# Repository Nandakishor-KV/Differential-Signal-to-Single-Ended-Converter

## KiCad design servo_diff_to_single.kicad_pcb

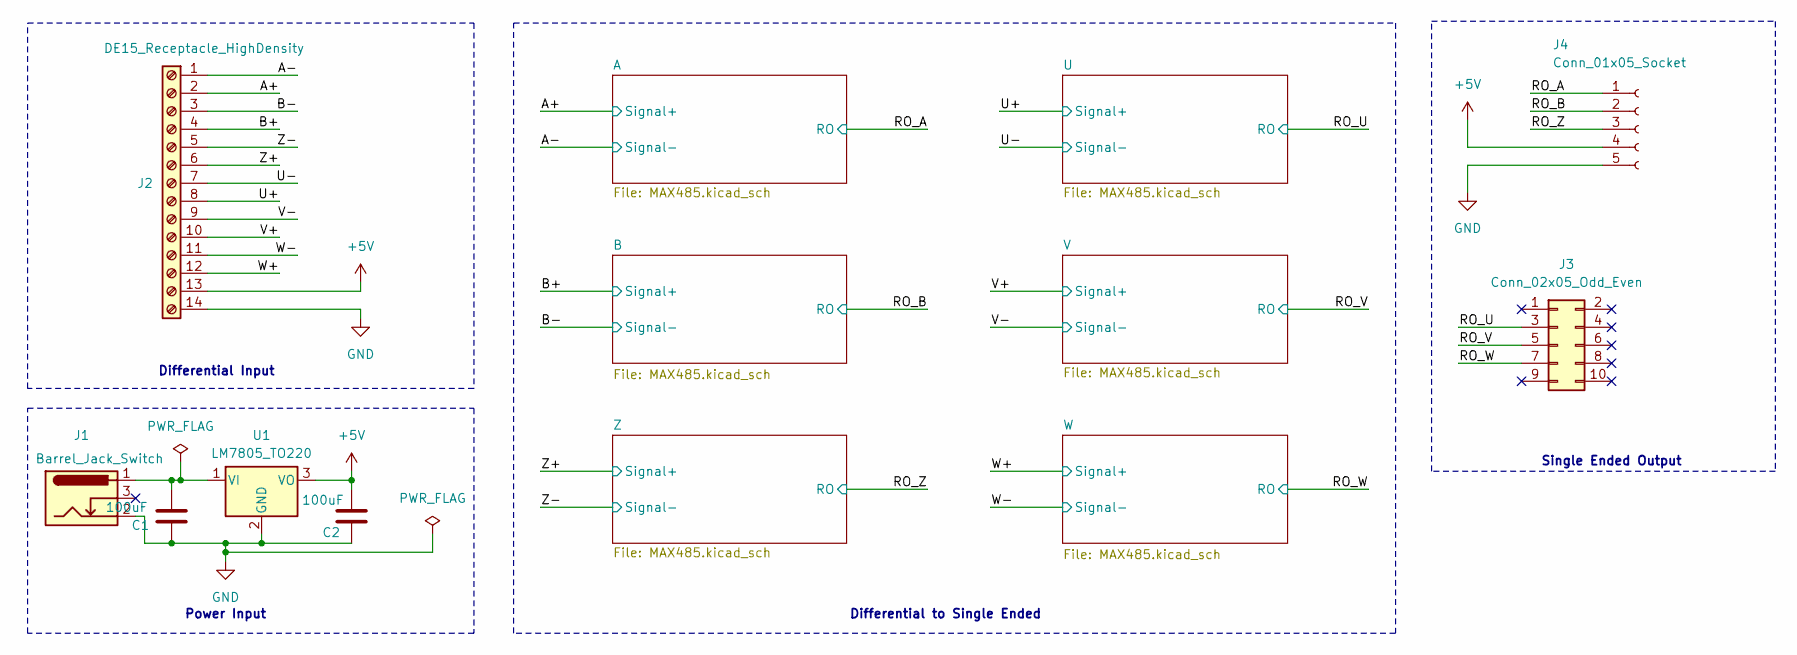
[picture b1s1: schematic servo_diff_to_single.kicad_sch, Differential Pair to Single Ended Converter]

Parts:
C1, C2: 100uF; CP_Radial_D6.3mm_P2.50mm
J1: Barrel_Jack_Switch; BarrelJack_Horizontal
J2: DE15_Receptacle_HighDensity; TerminalBlock_Phoenix_MKDS-3-14-5.08_1x14_P5.08mm_Horizontal
J3: Conn_02x05_Odd_Even; IDC-Header_2x05_P2.54mm_Vertical
J4: Conn_01x05_Socket; PinSocket_1x05_P2.54mm_Vertical
U1: LM7805_TO220; TO-220-3_Vertical_HS48_PL48_Heatsink_Without_mounting

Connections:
+5V: C2.1, J2.13, J4.4, U1.3 (VO); also elsewhere on the board
/A+: J2.2; also elsewhere on the board
/A-: J2.1; also elsewhere on the board
/B+: J2.4; also elsewhere on the board
/B-: J2.3; also elsewhere on the board
/RO_A: J4.1; also elsewhere on the board
/RO_B: J4.2; also elsewhere on the board
/RO_U: J3.3; also elsewhere on the board
/RO_V: J3.5; also elsewhere on the board
/RO_W: J3.7; also elsewhere on the board
/RO_Z: J4.3; also elsewhere on the board
/U+: J2.8; also elsewhere on the board
/U-: J2.7; also elsewhere on the board
/V+: J2.10; also elsewhere on the board
/V-: J2.9; also elsewhere on the board
/W+: J2.12; also elsewhere on the board
/W-: J2.11; also elsewhere on the board
/Z+: J2.6; also elsewhere on the board
/Z-: J2.5; also elsewhere on the board
GND: C1.2, C2.2, J1.2, J2.14, J4.5, U1.2 (GND); also elsewhere on the board
unnamed: C1.1, J1.1, U1.1 (VI)

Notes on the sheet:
Differential to Single Ended
Power Input
Single Ended Output
Differential Input

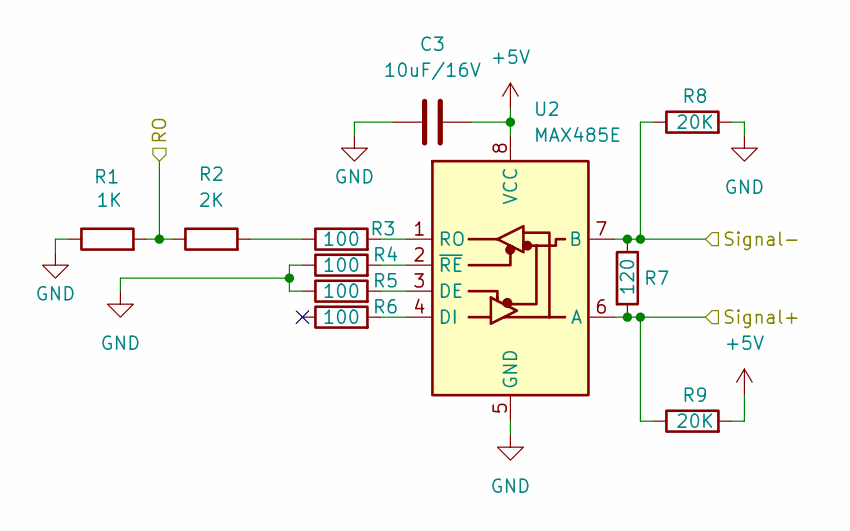
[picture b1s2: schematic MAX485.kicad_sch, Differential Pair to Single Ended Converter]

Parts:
C3: 10uF/16V; CP_Radial_D5.0mm_P2.50mm
R1: 1K; 0.25W_resistor
R2: 2K; 0.25W_resistor
R3, R4, R5, R6: 100; 0.25W_resistor
R7: 120; 0.25W_resistor
R8, R9: 20K; 0.25W_resistor
U2: MAX485E; SOIC-8_3.9x4.9mm_P1.27mm

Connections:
+5V: C3.1, R9.2, U2.8 (VCC); also elsewhere on the board
/A+: R7.2, R9.1, U2.6 (A); also elsewhere on the board
/A-: R7.1, R8.1, U2.7 (B); also elsewhere on the board
/RO_A: R1.2, R2.1; also elsewhere on the board
GND: C3.2, R1.1, R4.1, R5.1, R8.2, U2.5 (GND); also elsewhere on the board
unnamed: R2.2, R3.1
unnamed: R5.2, U2.3 (DE)
unnamed: R6.2, U2.4 (DI)
unnamed: R3.2, U2.1 (RO)
unnamed: R4.2, U2.2 (~RE)

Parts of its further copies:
C4, C5, C6, C7, C8: 10uF/16V; CP_Radial_D5.0mm_P2.50mm
R10, R19, R28, R37, R46: 1K; 0.25W_resistor
R11, R20, R29, R38, R47: 2K; 0.25W_resistor
R12, R13, R14, R15, R21, R22, R23, R24, R30, R31, R32, R33, R39, R40, R41, R42, R48, R49, R50, R51: 100; 0.25W_resistor
R16, R25, R34, R43, R52: 120; 0.25W_resistor
R17, R18, R26, R27, R35, R36, R44, R45, R53, R54: 20K; 0.25W_resistor
U3, U4, U5, U6, U7: MAX485E; SOIC-8_3.9x4.9mm_P1.27mm

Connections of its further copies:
+5V: C4.1, C5.1, C6.1, C7.1, C8.1, R18.2, R27.2, R36.2, R45.2, R54.2, U3.8 (VCC), U4.8 (VCC), U5.8 (VCC), U6.8 (VCC), U7.8 (VCC); also elsewhere on the board
/B+: R16.2, R18.1, U3.6 (A); also elsewhere on the board
/B-: R16.1, R17.1, U3.7 (B); also elsewhere on the board
/RO_B: R10.2, R11.1; also elsewhere on the board
/RO_U: R28.2, R29.1; also elsewhere on the board
/RO_V: R37.2, R38.1; also elsewhere on the board
/RO_W: R46.2, R47.1; also elsewhere on the board
/RO_Z: R19.2, R20.1; also elsewhere on the board
/U+: R34.2, R36.1, U5.6 (A); also elsewhere on the board
/U-: R34.1, R35.1, U5.7 (B); also elsewhere on the board
/V+: R43.2, R45.1, U6.6 (A); also elsewhere on the board
/V-: R43.1, R44.1, U6.7 (B); also elsewhere on the board
/W+: R52.2, R54.1, U7.6 (A); also elsewhere on the board
/W-: R52.1, R53.1, U7.7 (B); also elsewhere on the board
/Z+: R25.2, R27.1, U4.6 (A); also elsewhere on the board
/Z-: R25.1, R26.1, U4.7 (B); also elsewhere on the board
GND: C4.2, C5.2, C6.2, C7.2, C8.2, R10.1, R13.1, R14.1, R17.2, R19.1, R22.1, R23.1, R26.2, R28.1, R31.1, R32.1, R35.2, R37.1, R40.1, R41.1, R44.2, R46.1, R49.1, R50.1, R53.2, U3.5 (GND), U4.5 (GND), U5.5 (GND), U6.5 (GND), U7.5 (GND); also elsewhere on the board
unnamed: R11.2, R12.1
unnamed: R20.2, R21.1
unnamed: R29.2, R30.1
unnamed: R38.2, R39.1
unnamed: R47.2, R48.1
unnamed: R14.2, U3.3 (DE)
unnamed: R15.2, U3.4 (DI)
unnamed: R12.2, U3.1 (RO)
unnamed: R13.2, U3.2 (~RE)
unnamed: R23.2, U4.3 (DE)
unnamed: R24.2, U4.4 (DI)
unnamed: R21.2, U4.1 (RO)
unnamed: R22.2, U4.2 (~RE)
unnamed: R32.2, U5.3 (DE)
unnamed: R33.2, U5.4 (DI)
unnamed: R30.2, U5.1 (RO)
unnamed: R31.2, U5.2 (~RE)
unnamed: R41.2, U6.3 (DE)
unnamed: R42.2, U6.4 (DI)
unnamed: R39.2, U6.1 (RO)
unnamed: R40.2, U6.2 (~RE)
unnamed: R50.2, U7.3 (DE)
unnamed: R51.2, U7.4 (DI)
unnamed: R48.2, U7.1 (RO)
unnamed: R49.2, U7.2 (~RE)

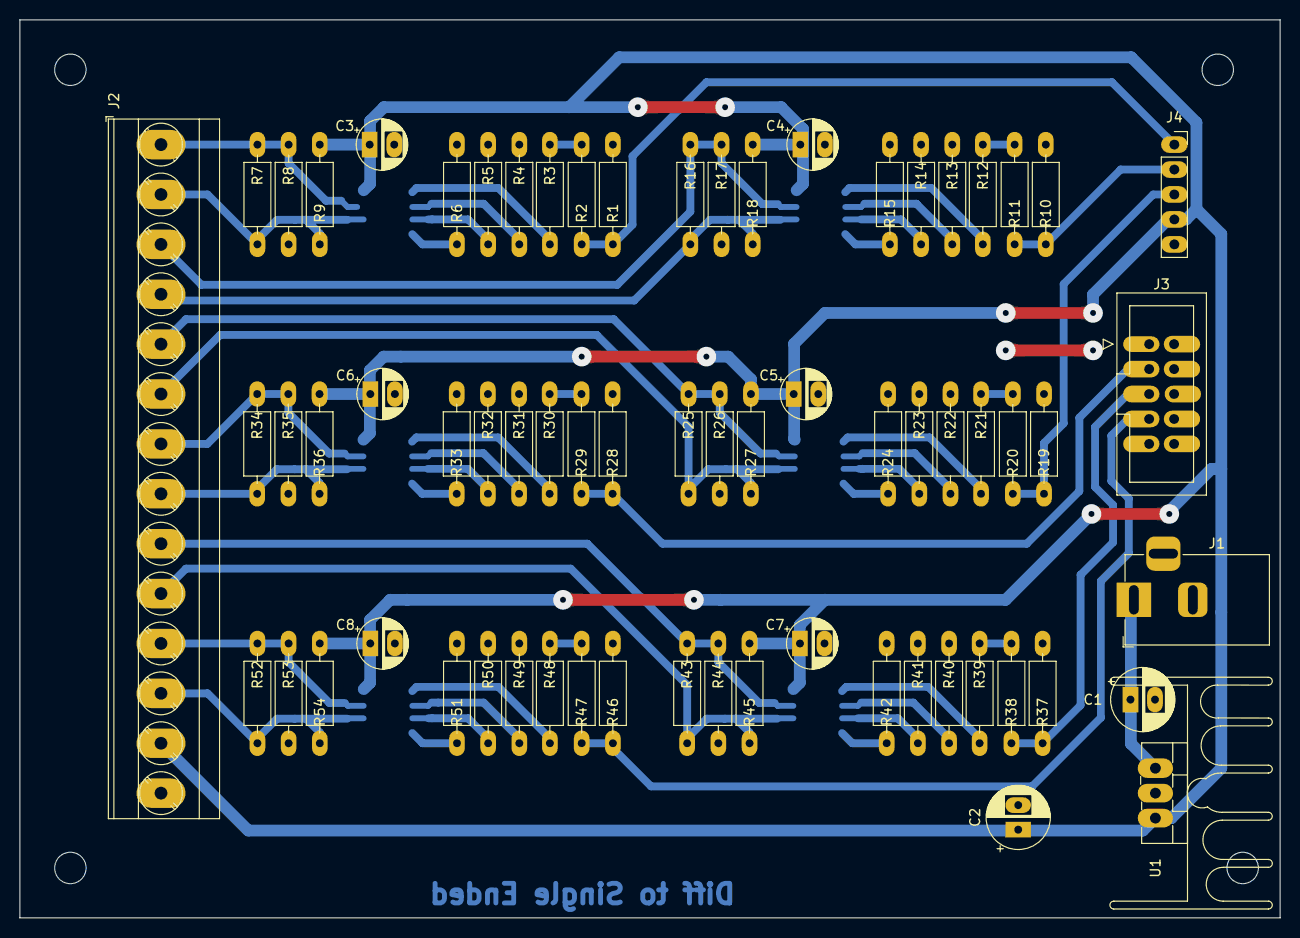
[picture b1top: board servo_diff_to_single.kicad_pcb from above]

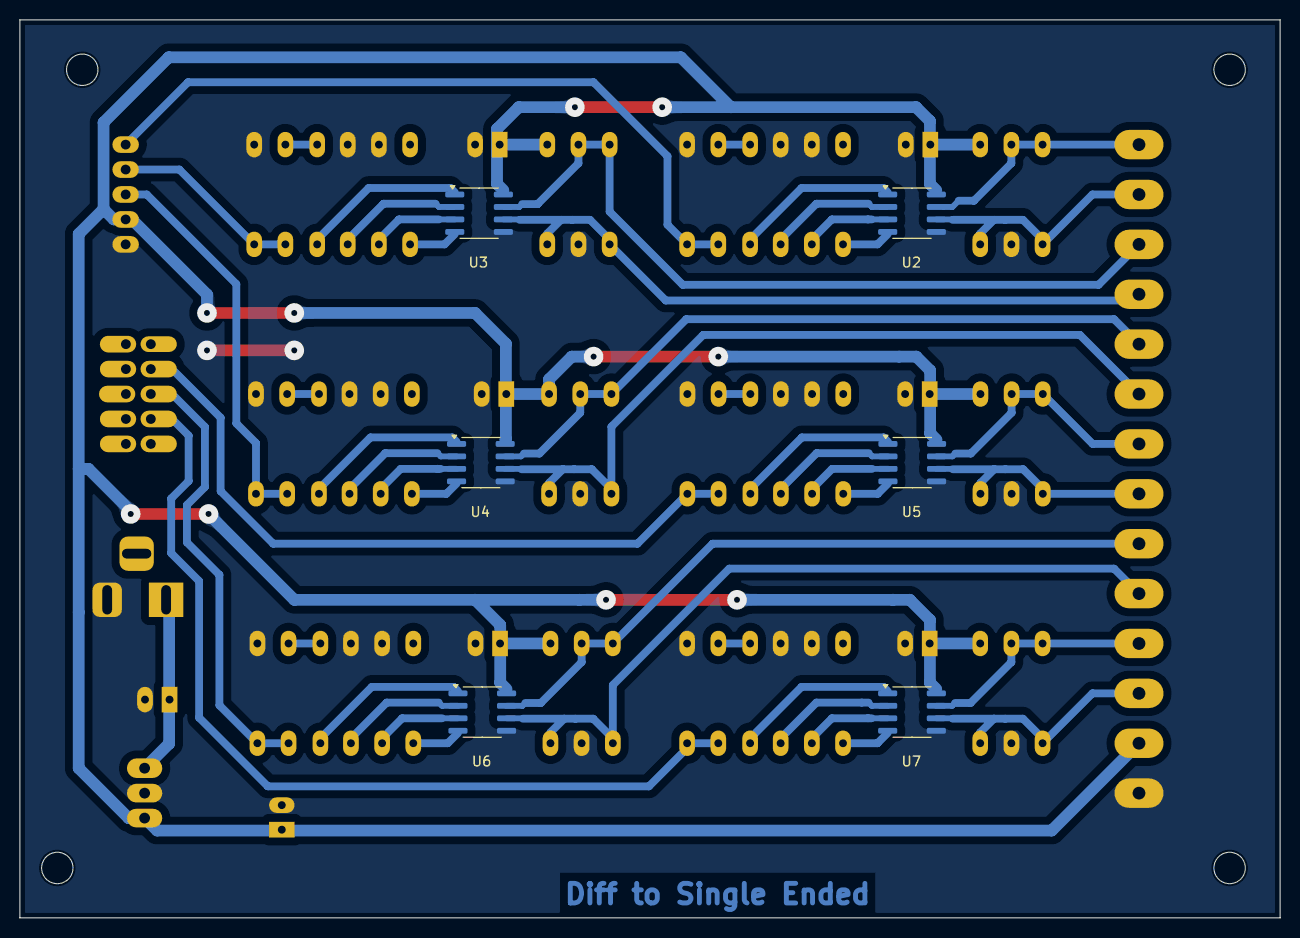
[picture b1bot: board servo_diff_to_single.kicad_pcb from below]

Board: 2 copper layers, 128.3 x 91.4 mm, 73 parts (6 on the bottom side), 51 nets.
